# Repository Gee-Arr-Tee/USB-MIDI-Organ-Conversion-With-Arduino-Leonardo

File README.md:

# USB-MIDI-Organ-Conversion-With-Arduino-Leonardo
How to Convert an Organ to a USB MIDI Controller to use with Hauptwerk / GrandOrgue or any DAW using 74HC165N Shift Registers.

All the Code and Eagle PCB and Schematic Files are provided, as well as connection diagrams and a Build of Materials (BOM).

Added the Gerber Files so anyone can get their own boards made.

Since an Arduino Leonardo does not have enough pins to control even a single 61 Note keyboard without using a diode matrix, shift registers are used as inputs for any extra pins required. 

A single board provides 32 Inputs which can be used for a Pedalboard and controlled by the Arduino with only 4 pins. 

Two boards can be linked to provide 64 Inputs, and controlled by only 4 pins also. 

Any object that can act as a switch can be used to trigger the Shift Registers and therefore play notes with, so it can be used on a hand made keyboard or group of switches etc., to construct a MIDI controller.

Using the boards to connect to an Arduino Leonardo, allows you to connect the devices directly to MIDI via the USB port, without having to change the bootloader. The Leonardo USB MIDI is detected by both Windows and Linux (if someone tries these on a Mac, I can update it on here). 

As a basis for for Project I used an old Baldwin 711 Organ, which has:
- Two 61 note keyboards.
- 25 Note Pedal Board.
- 30 Switches.
- Three Preset Buttons.
- One Analogue Pedal.

Using the Shift Registers PCBs, and this code with an Arduino Leonardo, it can handle:
 - Three 61 Note Keyboards.
 - 32 Note Pedal Board.
 - 32 Switches or Stops.
 - Nine Preset Buttons.
 - Two Analogue Pedals.

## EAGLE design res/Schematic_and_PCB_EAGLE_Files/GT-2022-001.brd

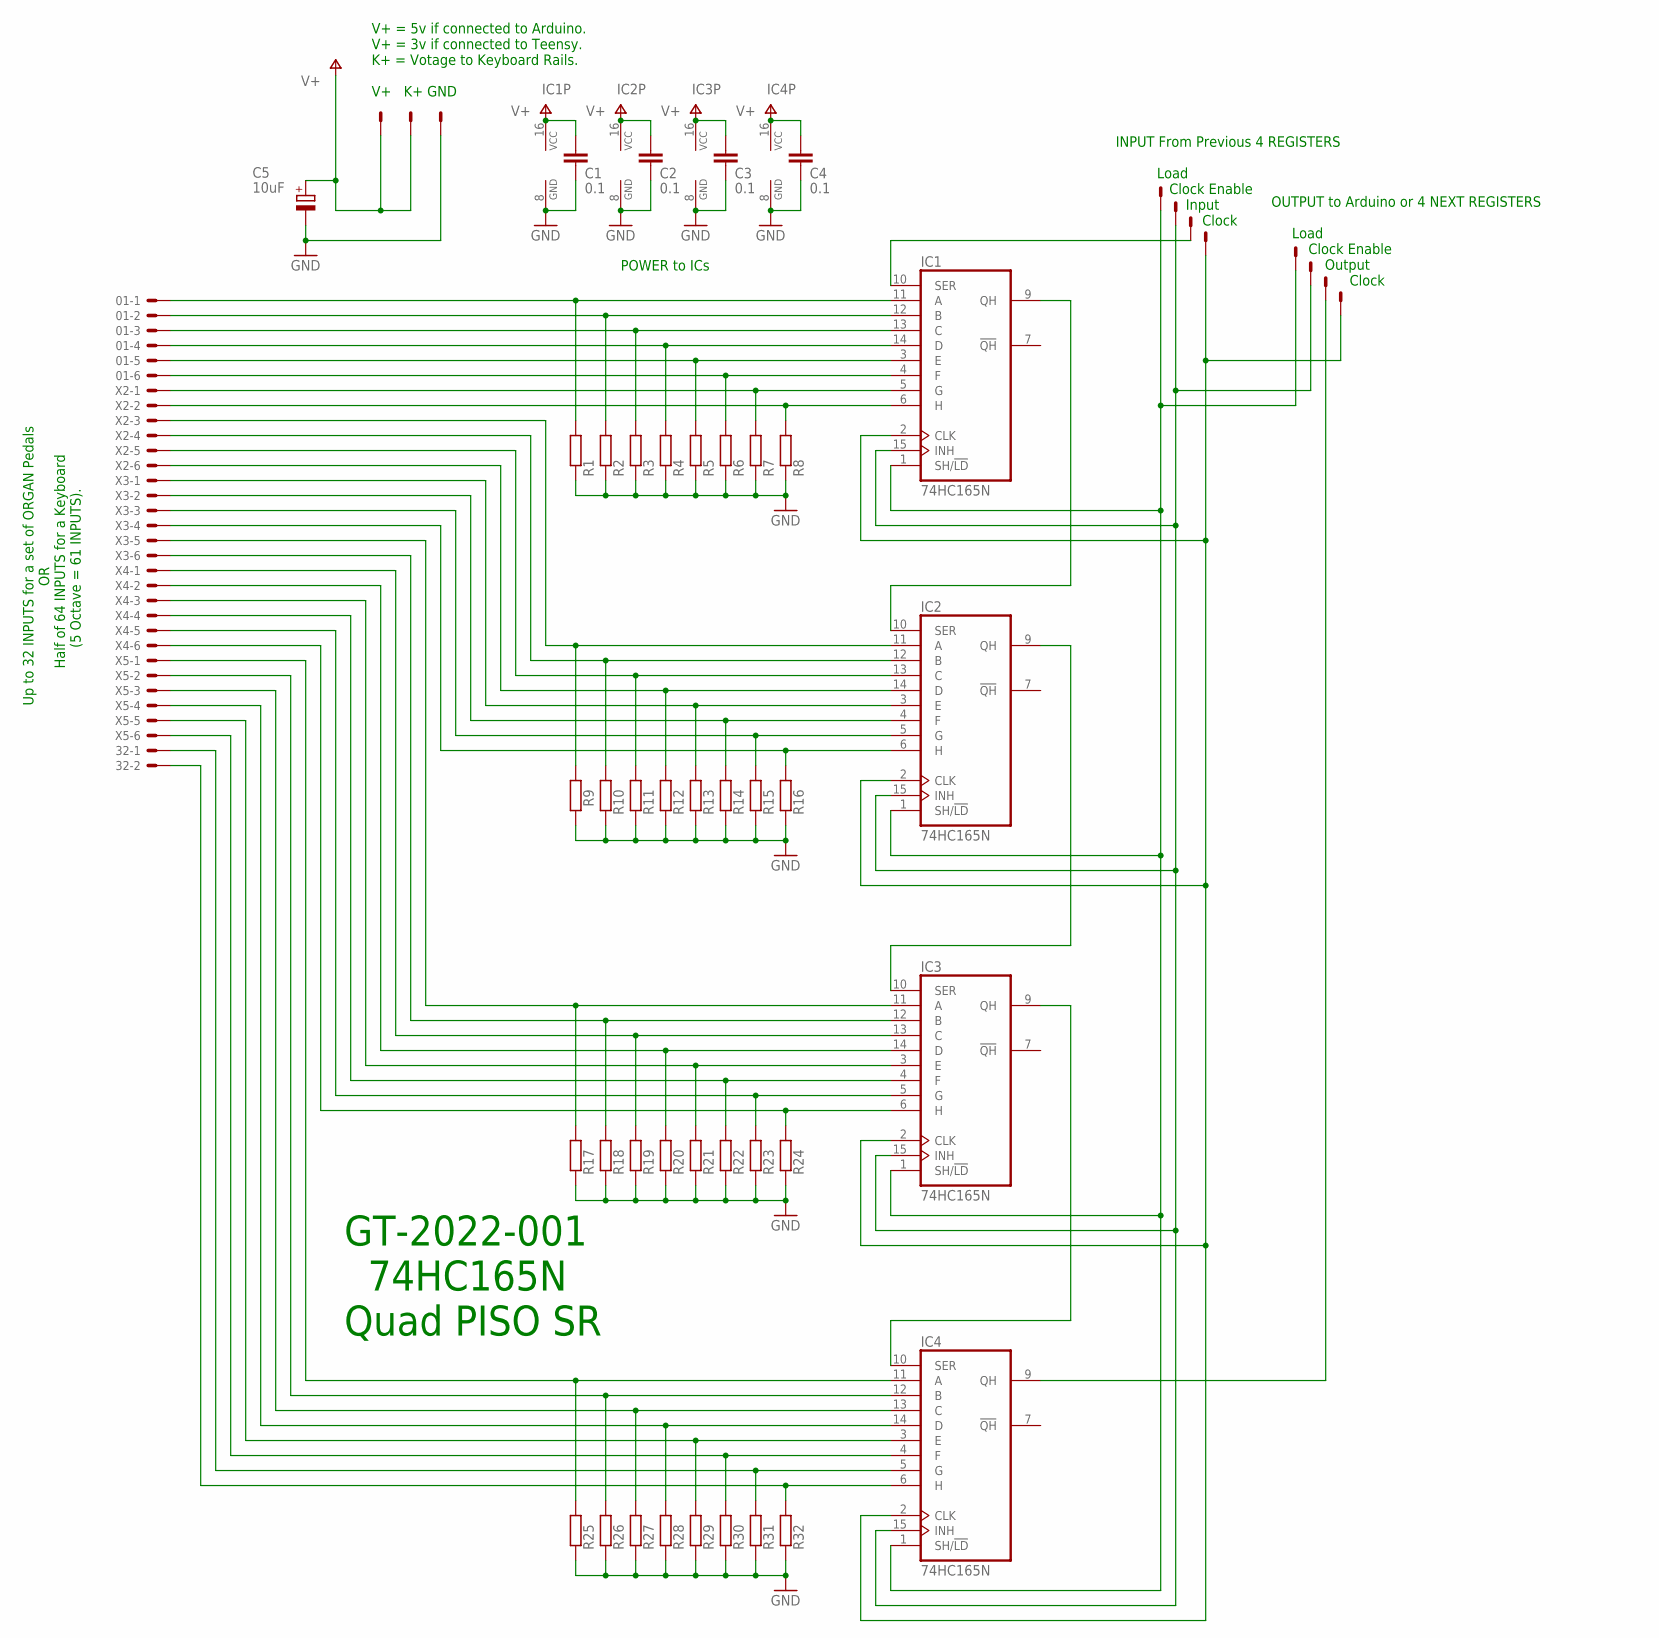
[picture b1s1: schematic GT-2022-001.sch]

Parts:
01: 22-23-2061
32: 22-23-2021
C1, C2, C3, C4: 0.1; C025-025X050
C5: 10uF; E2,5-7
IC1, IC2, IC3, IC4: 74HC165N; DIL16
LD_CE_IN_CK: 22-23-2041
LD_CE_OUT_CLK: 22-23-2041
R1, R2, R3, R4, R5, R6, R7, R8, R9, R10, R11, R12, R13, R14, R15, R16, R17, R18, R19, R20, R21, R22, R23, R24, R25, R26, R27, R28, R29, R30, R31, R32: R-EU_0204/7; 0204/7
V+_K+_GND: 22-23-2031
X2, X3, X4, X5: 22-23-2061

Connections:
GND: C1.2, C2.2, C3.2, C4.2, C5.-, IC1.8 (GND), IC2.8 (GND), IC3.8 (GND), IC4.8 (GND), R1.1, R2.1, R3.1, R4.1, R5.1, R6.1, R7.1, R8.1, R9.1, R10.1, R11.1, R12.1, R13.1, R14.1, R15.1, R16.1, R17.1, R18.1, R19.1, R20.1, R21.1, R22.1, R23.1, R24.1, R25.1, R26.1, R27.1, R28.1, R29.1, R30.1, R31.1, R32.1, V+_K+_GND.3
unnamed: IC1.5 (G), R7.2, X2.1
unnamed: 01.6, IC1.4 (F), R6.2
unnamed: 01.5, IC1.3 (E), R5.2
unnamed: 01.4, IC1.14 (D), R4.2
unnamed: 01.3, IC1.13 (C), R3.2
unnamed: 01.2, IC1.12 (B), R2.2
unnamed: 01.1, IC1.11 (A), R1.2
unnamed: IC2.6 (H), R16.2, X3.4
unnamed: IC4.4 (F), R30.2, X5.6
unnamed: IC3.12 (B), R18.2, X3.6
unnamed: IC3.11 (A), R17.2, X3.5
unnamed: IC4.14 (D), R28.2, X5.4
unnamed: IC1.1 (SH/!LD), IC2.1 (SH/!LD), IC3.1 (SH/!LD), IC4.1 (SH/!LD), LD_CE_IN_CK.1, LD_CE_OUT_CLK.1
unnamed: IC1.2 (CLK), IC2.2 (CLK), IC3.2 (CLK), IC4.2 (CLK), LD_CE_IN_CK.4, LD_CE_OUT_CLK.4
unnamed: IC1.10 (SER), LD_CE_IN_CK.3
unnamed: IC4.9 (QH), LD_CE_OUT_CLK.3
unnamed: IC4.11 (A), R25.2, X5.1
unnamed: IC1.6 (H), R8.2, X2.2
unnamed: IC1.9 (QH), IC2.10 (SER)
unnamed: IC2.9 (QH), IC3.10 (SER)
unnamed: IC1.15 (INH), IC2.15 (INH), IC3.15 (INH), IC4.15 (INH), LD_CE_IN_CK.2, LD_CE_OUT_CLK.2
unnamed: IC3.9 (QH), IC4.10 (SER)
unnamed: IC2.5 (G), R15.2, X3.3
unnamed: 32.1, IC4.5 (G), R31.2
unnamed: IC4.3 (E), R29.2, X5.5
unnamed: IC4.13 (C), R27.2, X5.3
unnamed: IC4.12 (B), R26.2, X5.2
unnamed: IC2.4 (F), R14.2, X3.2
unnamed: IC3.6 (H), R24.2, X4.6
unnamed: IC2.3 (E), R13.2, X3.1
unnamed: IC2.14 (D), R12.2, X2.6
unnamed: IC2.13 (C), R11.2, X2.5
unnamed: 32.2, IC4.6 (H), R32.2
unnamed: IC2.12 (B), R10.2, X2.4
unnamed: IC2.11 (A), R9.2, X2.3
unnamed: IC3.5 (G), R23.2, X4.5
unnamed: IC3.3 (E), R21.2, X4.3
unnamed: IC3.14 (D), R20.2, X4.2
unnamed: IC3.13 (C), R19.2, X4.1
unnamed: IC3.4 (F), R22.2, X4.4
V+: C1.1, C2.1, C3.1, C4.1, C5.+, IC1.16 (VCC), IC2.16 (VCC), IC3.16 (VCC), IC4.16 (VCC), V+_K+_GND.1, V+_K+_GND.2

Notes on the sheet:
INPUT From Previous 4 REGISTERS Load Clock Enable Input Clock
Up to 32 INPUTS for a set of ORGAN Pedals OR Half of 64 INPUTS for a Keyboard (5 Octave = 61 INPUTS).
V+ = 5v if connected to Arduino. V+ = 3v if connected to Teensy. K+ = Votage to Keyboard Rails. V+ K+ GND
OUTPUT to Arduino or 4 NEXT REGISTERS Load Clock Enable Output Clock
POWER to ICs
GT-2022-001 74HC165N Quad PISO SR

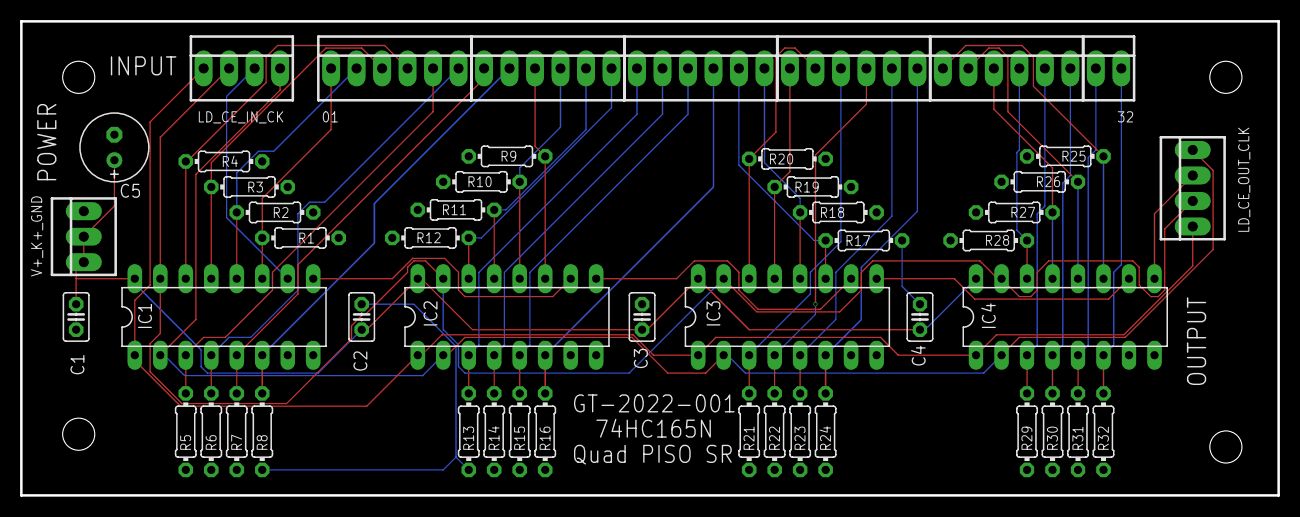
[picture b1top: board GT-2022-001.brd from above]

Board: 2 copper layers, 125.3 x 47.2 mm, 50 parts (0 on the bottom side), 42 nets.

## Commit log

2022-09-05 Create 1_keyboard
2022-09-05 Create temp
2022-09-12 Add files via upload
    How to Connect Keyboards, Pedalboards and Potentiometers to a standard Buss Bar and then to the Shift Register PCBs.
2022-09-12 Add files via upload
    Quad 74HC165N Shift Register Boards, created with Eagle v9.6.2
    The Boards can be used with the Arduino Leonardo Code provided, to make a keyboard or MIDI Controller from anything that acts as a switch.
2022-09-12 Add files via upload
    The Schematic and PCB Images of the Quad 74HC165N Shift Register Board, including the Build of Materials with images of the Components.
2022-10-25 Create Schematic_and_PCB_GERBER_Files
